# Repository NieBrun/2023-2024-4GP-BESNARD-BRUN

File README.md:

# 2023-2024 : Capteur low-tech Graphite (Niels Brun &amp; Paul Besnard)

## SOMMAIRE
*** 
  - [Contexte](#contexte)
  - [Livrables](#livrables)
  - [Matériel nécessaire](#matériel-nécessaire)
  - [1. Simulation électronique du capteur sous LTSpice](#simulation-électronique-du-capteur-sous-ltspice)
  - [2. Design du PCB sous KiCad](#design-du-pcb-sous-kicad)
  - [3. Code arduino](#code-arduino)
  - [4. Application android APK sous MIT App Inventor](#application-android-apk-sous-mit-app-inventor)
  - [5. Réalisation du shield](#réalisation-du-shield)
  - [6. Banc de test](#banc-de-test)
  - [7. Datasheet](#datasheet)
  - [Contact](#contact) 

*** 

## Contexte
&nbsp;&nbsp;&nbsp;&nbsp;&nbsp;&nbsp;Dans le cadre de l'UF "Du capteur au banc de test" se déroulant en 4ème année de Génie Physique de l’INSA Toulouse, nous avons développé un dispositif permettant de mesurer la contrainte. Le capteur du dispositif est basé sur l'article "Pencil Drawn Strain Gauges and Chemiresistors on Paper" (Cheng-Wei Lin*, Zhibo Zhao*, Jaemyung Kim & Jiaxing Huang). Il est simplement composé d'un bout de papier avec du crayon à papier. En déformant le papier, le nombre de particules de graphite composant le crayon à papier déposé sur le papier, reliées varie en fonction du type de déformation. Ce système granulaire subit une modification de résistance et de conductance. Grâce à cela, on  pourra remonter à la déformation tel une jauge de contrainte traditionnel. \
&nbsp;&nbsp;&nbsp;&nbsp;&nbsp;&nbsp;L'objectif est donc de pouvoir réaliser un dispositif permettant la mesure de déformation à partir d'un capteur low-tech. En passant par différentes étapes : simulations électroniques, design du PCB, code arduino et réalisation de datasheet.

## Livrables
- Un Shield PCB relié à une carte arduino UNO avec différents composants : un capteur graphite, un amplificateur transimpédance et un module bluetooth. Il peut également avoir un écran OLED, un flex sensor commercial, un potentiomètre digital, encodeur rotatoire ou des boutons.
- Un code arduino qui gère les différents composants cités précédemments (mesures de contraintes, échanges bluetooth et OLED, potentiomètre digital et boutons)
- Une application Android (sous MIT App Inventor) interfaçant le PCB et le code arduino.
- Un code arduino réalisant les essais de banc de test sur les mesures de contraintes.
- Une datasheet sur le capteur de contrainte.

Nous avons opté pour l'ajout d'un écran OLED, du flex sensor commercial, du potentiomètre digital. Egalement, nous avons choisi l'implémentation de 3 boutons plutôt que de l'encodeur rotatoire.

## Matériel nécessaire
Pour réaliser notre dispositif électronique, voici la liste des composants nécessaires :

- Résistances : 2 de 1 kOhms, 5 de 10 kOhms, 2 de 100 kOhms
- Capacités : 2 de 100 nF, 1 de 1 uF
- Arduino Uno
- Amplificateur opérationnel LTC1050
- Potentiomètre digital MCP41500
- Module Bluetooth HC05
- Ecran OLED 128x64
- Flex Sensor
- 3 boutons

## Simulation électronique du capteur sous LTSpice

## Design du PCB sous KiCad

## Code arduino

## Application android APK sous MIT App Inventor

## Réalisation du shield

## Banc de test

## Datasheet

## Contact

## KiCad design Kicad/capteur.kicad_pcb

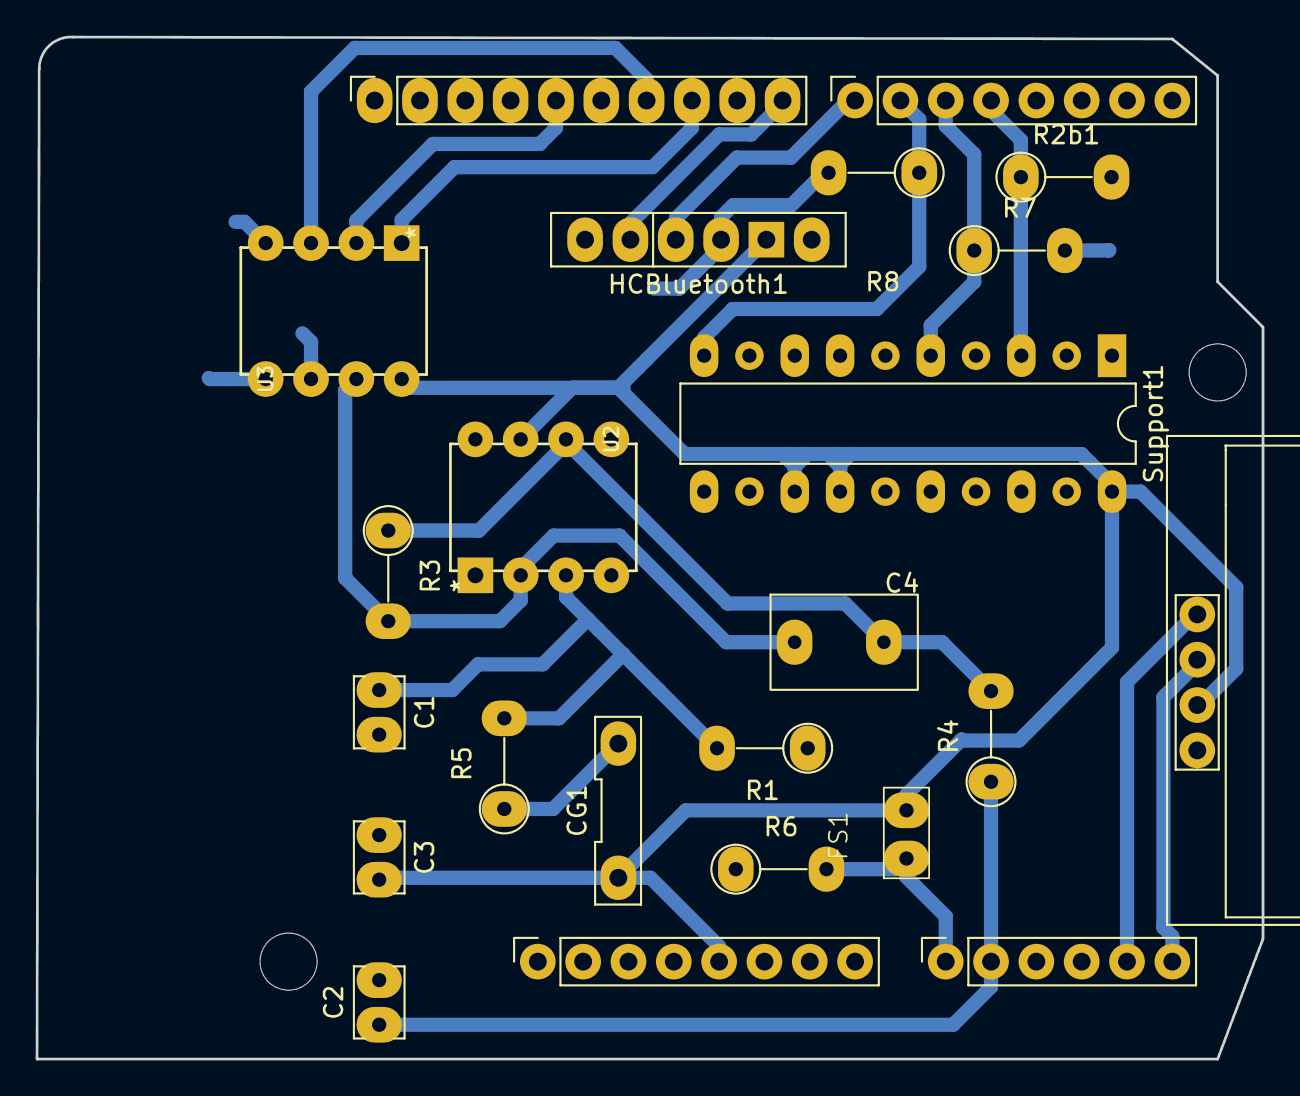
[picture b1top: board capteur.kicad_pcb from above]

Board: 2 copper layers, 68.7 x 57.3 mm, 25 parts (0 on the bottom side), 18 nets.

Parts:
Brd1: SSD1306; 128x64OLED
C1, C2, C3: C; capa
C4: C; C4
CG1: CG
FS1: FlexSensor
HCBluetooth1: Bluetooth_HC-05
J1: Power; PinSocket_1x08_P2.54mm_Vertical
J2: Digital/PWM; PinSocket_1x10_P2.54mm_Vertical
J3: Analog; PinSocket_1x06_P2.54mm_Vertical
J4: Digital/PWM; PinSocket_1x08_P2.54mm_Vertical
MH2, MH3: MountingHole_3.2mm
R1, R2b1, R3, R4, R5, R6, R7, R8: R; R_Axial_DIN0207_L6.3mm_D2.5mm_P5.08mm_Vertical
Support1: DIP-20_W7.62mm_LongPads
U2: LTC1050ACN8; LTC
U3: MCP41100; LTC

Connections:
+5V: Brd1.2 (VCC), C3.2, CG1.1 (Vcc), FS1.2 (Vcc), HCBluetooth1.4 (Vcc), J1.5, Support1.1 (Vcc), Support1.4 (Vcc), Support1.5 (Vcc), U2.7 (V+), U3.8 (VDD)
/4: J4.4, R2b1.1, Support1.2 (Out)
/7: HCBluetooth1.2 (TX), J4.1
/8: HCBluetooth1.1 (RX), J2.10
/13: J2.5, U3.2 (SCK)
/*5: J4.3, R7.1, Support1.3 (Out)
/*6: J4.2, R8.1, Support1.6 (Out)
/*10: J2.8, U3.1 (~CS)
/*11: J2.7, U3.3 (SI)
/A0: FS1.1 (Vout), J3.1, R6.2
/A1: C2.1, J3.2, R4.1
/R2: C4.1, R3.2, U2.2 (-IN), U3.7 (PB0)
/SCL/A5: Brd1.3 (SCL), J2.1, J3.6
/SDA/A4: Brd1.4 (SDA), J2.2, J3.5
GND: Brd1.1 (GND), C1.2, C2.2, C3.1, HCBluetooth1.3 (GND), J1.6, J1.7, J2.4, R1.1, R2b1.2, R6.1, R7.2, R8.2, U2.4 (V-), U3.4 (VSS), U3.5 (PA0), U3.6 (PW0)
unnamed: CG1.2 (Vout), R5.1
unnamed: C1.1, R1.2, R5.2, U2.3 (+IN)
unnamed: C4.2, R3.1, R4.2, U2.6 (OUT)

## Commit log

2024-03-17 Add of kicad
2024-03-17 Add of test program
2024-03-17 Add of main file, manage all components and android apk
    Not the final version: android apk need fix and so arduino (probably). Optimisation of MesureINST, MesureMoyenne and FlexSensor possible (all OLED stuff). Care to RAM usage due to OLED screen which i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
2024-03-18 Small changes of kicad
2024-03-18 add of informations in readme
2024-03-19 Ajout du calcul de résistance du capteur, à compléter
2024-03-21 Add of comments and calculation of graphite sensor resistance
2024-03-23 minor change of kicad schematic
2024-03-23 Create Capteur
    trying to upload images

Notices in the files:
parts and their libraries:
COPYRIGHT: Copyright C 2016 Accelerated Designs. All rights reserved
